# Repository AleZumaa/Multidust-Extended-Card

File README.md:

# Multidust-Extended-Card

## Placa Extensora / Breakout de Pruebas (Test Adapter Board)

Placa de circuito impreso (PCB) diseñada como interfaz de interconexión y depuración para medición, ruteo y diagnóstico de señales. Permite derivar conectores multicable de cinta plana (IDC / HE10) hacia puntos de prueba o pines header individuales (J1 a J130), facilitando el conexionado con osciloscopios, analizadores lógicos, multímetros o protoboards.

---

## 🛠️ Herramientas de Diseño (EDA)

* **Software:** [KiCad EDA](https://www.kicad.org/)
* **Versión:** `v10.0.1`

> ℹ️ **Nota de compatibilidad:** El esquema y el layout fueron diseñados con **KiCad 10.0.1**. Para abrir y editar los archivos de proyecto sin problemas de migración de footprints o bibliotecas de símbolos, se recomienda utilizar KiCad 10.0.1 o superior.

---

## 📋 Características Principales

- **Conectores Principales:**
  - `CONN-1`: IDC / HE10 hembra/macho de **40 pines** (`HE10-40-1`).
  - `CONN-2`: IDC / HE10 hembra/macho de **40 pines** (`HE10-40-2`).
  - `CONN-3`: IDC / HE10 hembra/macho de **40 pines** (`HE10-40-3`).
  - `CONN-4`: IDC / HE10 hembra/macho de **10 pines** (`HE10-10`).
- **Puntos de Medición / Breakout:**
  - 130 terminales individuales tipo pad / pin-header paso 2.54 mm (`J1` a `J130`).
  - Distribución en doble hilera perimétrica (izquierda/derecha) con pads cuadrados/redondos para facilitar la colocación de puntas de prueba o pines macho/hembra.
- **Topología de PCB:**
  - Placa de 2 capas (*Double-sided FR4*).
  - Pistas con trazado a 45° optimizado para mantener integridad de señal básica y separación uniforme.
  - Indicadores serigrafiados de orientación (flechas triangulares en pin 1 de cada conector IDC).

---

## 📐 Especificaciones Técnicas

| Parámetro | Valor / Descripción |
| :--- | :--- |
| **Tipo de Placa** | Breakout / Adapter / Test Board |
| **Software EDA** | **KiCad v10.0.1** |
| **Capas** | 2 capas (Top / Bottom) |
| **Material sugerido** | FR-4 estándar (1.6 mm espesor) |
| **Acabado sugerido** | HASL Lead-Free o ENIG (recomendado para pads de prueba) |
| **Paso de Conectores IDC** | 2.54 mm (0.1") |
| **Paso de Headers de Prueba** | 2.54 mm (0.1") estándar |
| **Capacidad de Señal** | Señales lógicas, buses digitales (GPIO, SPI, UART, I2C, bus paralelo) y alimentación de baja corriente |

---

## 🔌 Asignación de Conectores y Ruteo

| Conector | Tipo / Descripción | Rango de Pines Breakout |
| :---: | :---: | :---: |
| **CONN-1** | HE10-40 (40 pines) | `J1` – `J40` |
| **CONN-2** | HE10-40 (40 pines) | `J41` – `J80` |
| **CONN-3** | HE10-40 (40 pines) | `J81` – `J120` |
| **CONN-4** | HE10-10 (10 pines) | `J121` – `J130` |

> ⚠️ **Nota:** Verificar siempre la correspondencia entre la serigrafía (flecha de pin 1 en `CONN-1..4`) y la muesca polarizadora del cable plano IDC antes de alimentar el circuito bajo prueba.

---

## 🛠️ Lista de Materiales (BOM)

| Designador | Cantidad | Componente / Descripción | Encapsulado / Footprint |
| :--- | :---: | :--- | :--- |
| `CONN-1`, `CONN-2`, `CONN-3` | 3 | Conector Header tipo caja IDC 40 pines (2x20) paso 2.54 mm | Through-Hole (THT) 2.54 mm |
| `CONN-4` | 1 | Conector Header tipo caja IDC 10 pines (2x5) paso 2.54 mm | Through-Hole (THT) 2.54 mm |
| `J1` - `J130` | 130 | Tiras de pines hembra o macho / Puntos de prueba (Test Points) | Pad / THT individual 2.54 mm |

---

## 📁 Estructura del Repositorio

```text
├── Hardware/
│   ├── Schematics/         # Esquemáticos en formato KiCad v10.0.1 (.kicad_sch)
│   ├── PCB/                # Archivo de PCB KiCad v10.0.1 (.kicad_pcb)
│   └── Gerbers/            # Archivos de fabricación (Gerber RS-274X, Drill files)
├── Docs/
│   ├── Pinout_Mapping.csv  # Mapeo detallado señal por señal
│   └── Dimensions.pdf      # Plano mecánico acotado
└── README.md
```

---

## 📄 Licencia

Este hardware se distribuye bajo licencia libre [CERN-OHL-P](https://ohwr.org/cern_ohl_p_v2.txt) (Open Hardware Licence Permissive) o [MIT License](LICENSE).

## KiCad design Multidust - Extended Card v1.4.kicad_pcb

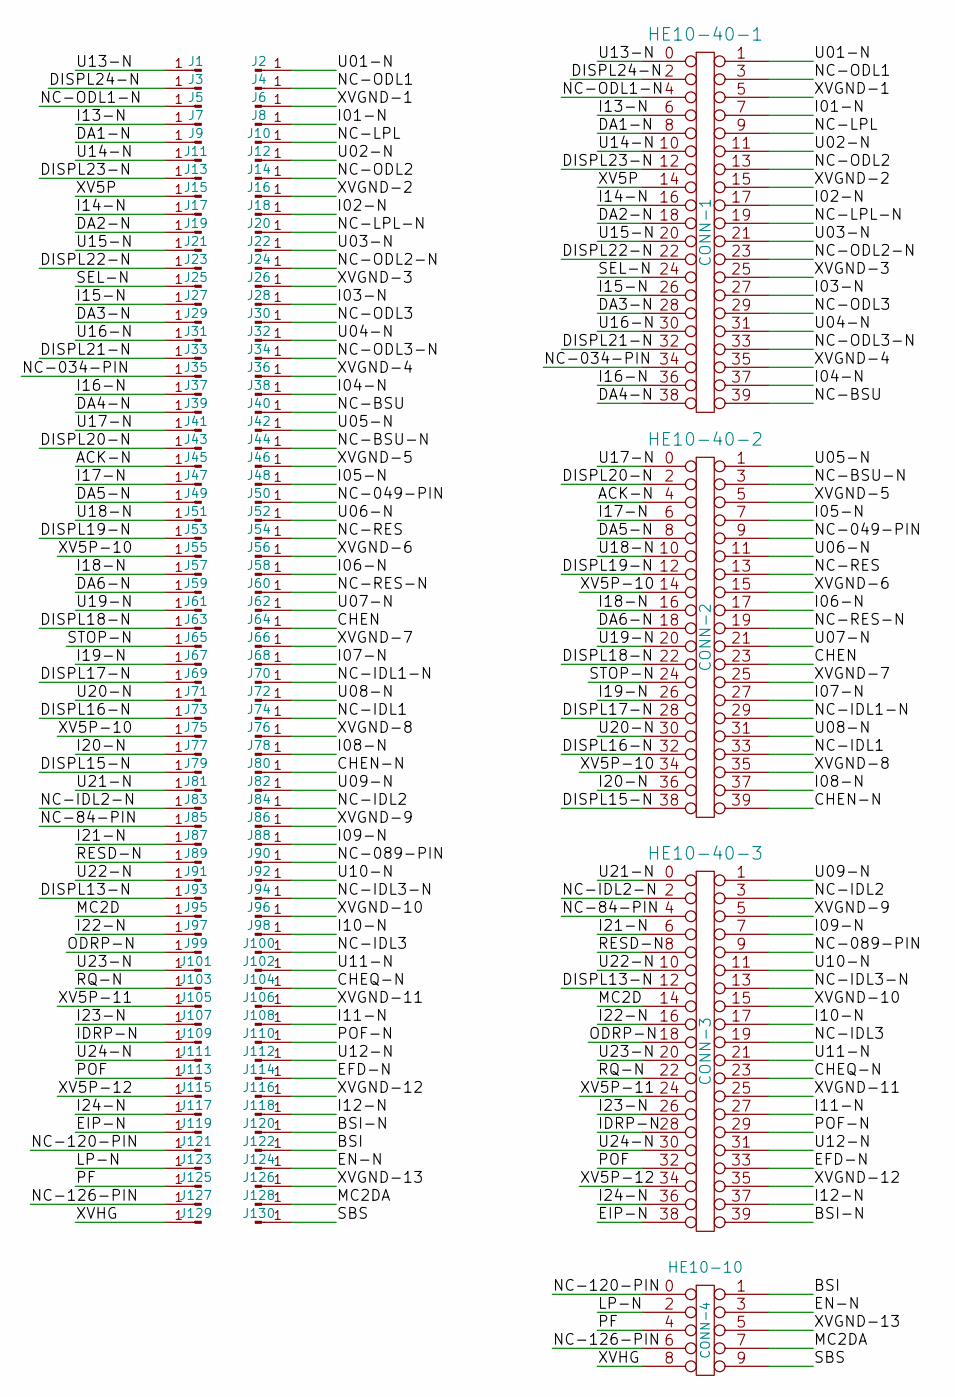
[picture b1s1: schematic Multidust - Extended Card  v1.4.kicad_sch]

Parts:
HE10-10: CONN-4; he10-10
HE10-40-1: CONN-1; he10-40
HE10-40-2: CONN-2; he10-40
HE10-40-3: CONN-3; he10-40
J1, J2, J3, J4, J5, J6, J7, J8, J9, J10, J11, J12, J13, J14, J15, J16, J17, J18, J19, J20, J21, J22, J23, J24, J25, J26, J27, J28, J29, J30, J31, J32, J33, J34, J35, J36, J37, J38, J39, J40, J41, J42, J43, J44, J45, J46, J47, J48, J49, J50, J51, J52, J53, J54, J55, J56, J57, J58, J59, J60, J61, J62, J63, J64, J65, J66, J67, J68, J69, J70, J71, J72, J73, J74, J75, J76, J77, J78, J79, J80, J81, J82, J83, J84, J85, J86, J87, J88, J89, J90, J91, J92, J93, J94, J95, J96, J97, J98, J99, J100, J101, J102, J103, J104, J105, J106, J107, J108, J109, J110, J111, J112, J113, J114, J115, J116, J117, J118, J119, J120, J121, J122, J123, J124, J125, J126, J127, J128, J129, J130: Conn_01x01_Pin; PinHeader_1x01_Oval_Grande

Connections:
/ACK-N: HE10-40-2.4, J45.1 (Pin_1_1)
/BSI: HE10-10.1, J122.1 (Pin_1_1)
/BSI-N: HE10-40-3.39, J120.1 (Pin_1_1)
/CHEN: HE10-40-2.23, J64.1 (Pin_1_1)
/CHEN-N: HE10-40-2.39, J80.1 (Pin_1_1)
/CHEQ-N: HE10-40-3.23, J104.1 (Pin_1_1)
/DA1-N: HE10-40-1.8, J9.1 (Pin_1_1)
/DA2-N: HE10-40-1.18, J19.1 (Pin_1_1)
/DA3-N: HE10-40-1.28, J29.1 (Pin_1_1)
/DA4-N: HE10-40-1.38, J39.1 (Pin_1_1)
/DA5-N: HE10-40-2.8, J49.1 (Pin_1_1)
/DA6-N: HE10-40-2.18, J59.1 (Pin_1_1)
/DISPL13-N: HE10-40-3.12, J93.1 (Pin_1_1)
/DISPL15-N: HE10-40-2.38, J79.1 (Pin_1_1)
/DISPL16-N: HE10-40-2.32, J73.1 (Pin_1_1)
/DISPL17-N: HE10-40-2.28, J69.1 (Pin_1_1)
/DISPL18-N: HE10-40-2.22, J63.1 (Pin_1_1)
/DISPL19-N: HE10-40-2.12, J53.1 (Pin_1_1)
/DISPL20-N: HE10-40-2.2, J43.1 (Pin_1_1)
/DISPL21-N: HE10-40-1.32, J33.1 (Pin_1_1)
/DISPL22-N: HE10-40-1.22, J23.1 (Pin_1_1)
/DISPL23-N: HE10-40-1.12, J13.1 (Pin_1_1)
/DISPL24-N: HE10-40-1.2, J3.1 (Pin_1_1)
/EFD-N: HE10-40-3.33, J114.1 (Pin_1_1)
/EIP-N: HE10-40-3.38, J119.1 (Pin_1_1)
/EN-N: HE10-10.3, J124.1 (Pin_1_1)
/I01-N: HE10-40-1.7, J8.1 (Pin_1_1)
/I02-N: HE10-40-1.17, J18.1 (Pin_1_1)
/I03-N: HE10-40-1.27, J28.1 (Pin_1_1)
/I04-N: HE10-40-1.37, J38.1 (Pin_1_1)
/I05-N: HE10-40-2.7, J48.1 (Pin_1_1)
/I06-N: HE10-40-2.17, J58.1 (Pin_1_1)
/I07-N: HE10-40-2.27, J68.1 (Pin_1_1)
/I08-N: HE10-40-2.37, J78.1 (Pin_1_1)
/I09-N: HE10-40-3.7, J88.1 (Pin_1_1)
/I10-N: HE10-40-3.17, J98.1 (Pin_1_1)
/I11-N: HE10-40-3.27, J108.1 (Pin_1_1)
/I12-N: HE10-40-3.37, J118.1 (Pin_1_1)
/I13-N: HE10-40-1.6, J7.1 (Pin_1_1)
/I14-N: HE10-40-1.16, J17.1 (Pin_1_1)
/I15-N: HE10-40-1.26, J27.1 (Pin_1_1)
/I16-N: HE10-40-1.36, J37.1 (Pin_1_1)
/I17-N: HE10-40-2.6, J47.1 (Pin_1_1)
/I18-N: HE10-40-2.16, J57.1 (Pin_1_1)
/I19-N: HE10-40-2.26, J67.1 (Pin_1_1)
/I20-N: HE10-40-2.36, J77.1 (Pin_1_1)
/I21-N: HE10-40-3.6, J87.1 (Pin_1_1)
/I22-N: HE10-40-3.16, J97.1 (Pin_1_1)
/I23-N: HE10-40-3.26, J107.1 (Pin_1_1)
/I24-N: HE10-40-3.36, J117.1 (Pin_1_1)
/IDRP-N: HE10-40-3.28, J109.1 (Pin_1_1)
/LP-N: HE10-10.2, J123.1 (Pin_1_1)
/MC2D: HE10-40-3.14, J95.1 (Pin_1_1)
/MC2DA: HE10-10.7, J128.1 (Pin_1_1)
/NC-034-PIN: HE10-40-1.34, J35.1 (Pin_1_1)
/NC-049-PIN: HE10-40-2.9, J50.1 (Pin_1_1)
/NC-84-PIN: HE10-40-3.4, J85.1 (Pin_1_1)
/NC-089-PIN: HE10-40-3.9, J90.1 (Pin_1_1)
/NC-120-PIN: HE10-10.0, J121.1 (Pin_1_1)
/NC-126-PIN: HE10-10.6, J127.1 (Pin_1_1)
/NC-BSU: HE10-40-1.39, J40.1 (Pin_1_1)
/NC-BSU-N: HE10-40-2.3, J44.1 (Pin_1_1)
/NC-IDL1: HE10-40-2.33, J74.1 (Pin_1_1)
/NC-IDL1-N: HE10-40-2.29, J70.1 (Pin_1_1)
/NC-IDL2: HE10-40-3.3, J84.1 (Pin_1_1)
/NC-IDL2-N: HE10-40-3.2, J83.1 (Pin_1_1)
/NC-IDL3: HE10-40-3.19, J100.1 (Pin_1_1)
/NC-IDL3-N: HE10-40-3.13, J94.1 (Pin_1_1)
/NC-LPL: HE10-40-1.9, J10.1 (Pin_1_1)
/NC-LPL-N: HE10-40-1.19, J20.1 (Pin_1_1)
/NC-ODL1: HE10-40-1.3, J4.1 (Pin_1_1)
/NC-ODL1-N: HE10-40-1.4, J5.1 (Pin_1_1)
/NC-ODL2: HE10-40-1.13, J14.1 (Pin_1_1)
/NC-ODL2-N: HE10-40-1.23, J24.1 (Pin_1_1)
/NC-ODL3: HE10-40-1.29, J30.1 (Pin_1_1)
/NC-ODL3-N: HE10-40-1.33, J34.1 (Pin_1_1)
/NC-RES: HE10-40-2.13, J54.1 (Pin_1_1)
/NC-RES-N: HE10-40-2.19, J60.1 (Pin_1_1)
/ODRP-N: HE10-40-3.18, J99.1 (Pin_1_1)
/PF: HE10-10.4, J125.1 (Pin_1_1)
/POF: HE10-40-3.32, J113.1 (Pin_1_1)
/POF-N: HE10-40-3.29, J110.1 (Pin_1_1)
/RESD-N: HE10-40-3.8, J89.1 (Pin_1_1)
/RQ-N: HE10-40-3.22, J103.1 (Pin_1_1)
/SBS: HE10-10.9, J130.1 (Pin_1_1)
/SEL-N: HE10-40-1.24, J25.1 (Pin_1_1)
/STOP-N: HE10-40-2.24, J65.1 (Pin_1_1)
/U01-N: HE10-40-1.1, J2.1 (Pin_1_1)
/U02-N: HE10-40-1.11, J12.1 (Pin_1_1)
/U03-N: HE10-40-1.21, J22.1 (Pin_1_1)
/U04-N: HE10-40-1.31, J32.1 (Pin_1_1)
/U05-N: HE10-40-2.1, J42.1 (Pin_1_1)
/U06-N: HE10-40-2.11, J52.1 (Pin_1_1)
/U07-N: HE10-40-2.21, J62.1 (Pin_1_1)
/U08-N: HE10-40-2.31, J72.1 (Pin_1_1)
/U09-N: HE10-40-3.1, J82.1 (Pin_1_1)
/U10-N: HE10-40-3.11, J92.1 (Pin_1_1)
/U11-N: HE10-40-3.21, J102.1 (Pin_1_1)
/U12-N: HE10-40-3.31, J112.1 (Pin_1_1)
/U13-N: HE10-40-1.0, J1.1 (Pin_1_1)
/U14-N: HE10-40-1.10, J11.1 (Pin_1_1)
/U15-N: HE10-40-1.20, J21.1 (Pin_1_1)
/U16-N: HE10-40-1.30, J31.1 (Pin_1_1)
/U17-N: HE10-40-2.0, J41.1 (Pin_1_1)
/U18-N: HE10-40-2.10, J51.1 (Pin_1_1)
/U19-N: HE10-40-2.20, J61.1 (Pin_1_1)
/U20-N: HE10-40-2.30, J71.1 (Pin_1_1)
/U21-N: HE10-40-3.0, J81.1 (Pin_1_1)
/U22-N: HE10-40-3.10, J91.1 (Pin_1_1)
/U23-N: HE10-40-3.20, J101.1 (Pin_1_1)
/U24-N: HE10-40-3.30, J111.1 (Pin_1_1)
/XV5P: HE10-40-1.14, J15.1 (Pin_1_1)
/XV5P-3: HE10-40-3.24, J105.1 (Pin_1_1)
/XV5P-4: HE10-40-3.34, J115.1 (Pin_1_1)
/XVGND-1: HE10-40-1.5, J6.1 (Pin_1_1)
/XVGND-2: HE10-40-1.15, J16.1 (Pin_1_1)
/XVGND-3: HE10-40-1.25, J26.1 (Pin_1_1)
/XVGND-4: HE10-40-1.35, J36.1 (Pin_1_1)
/XVGND-5: HE10-40-2.5, J46.1 (Pin_1_1)
/XVGND-6: HE10-40-2.15, J56.1 (Pin_1_1)
/XVGND-7: HE10-40-2.25, J66.1 (Pin_1_1)
/XVGND-8: HE10-40-2.35, J76.1 (Pin_1_1)
/XVGND-9: HE10-40-3.5, J86.1 (Pin_1_1)
/XVGND-10: HE10-40-3.15, J96.1 (Pin_1_1)
/XVGND-11: HE10-40-3.25, J106.1 (Pin_1_1)
/XVGND-12: HE10-40-3.35, J116.1 (Pin_1_1)
/XVGND-13: HE10-10.5, J126.1 (Pin_1_1)
/XVHG: HE10-10.8, J129.1 (Pin_1_1)

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
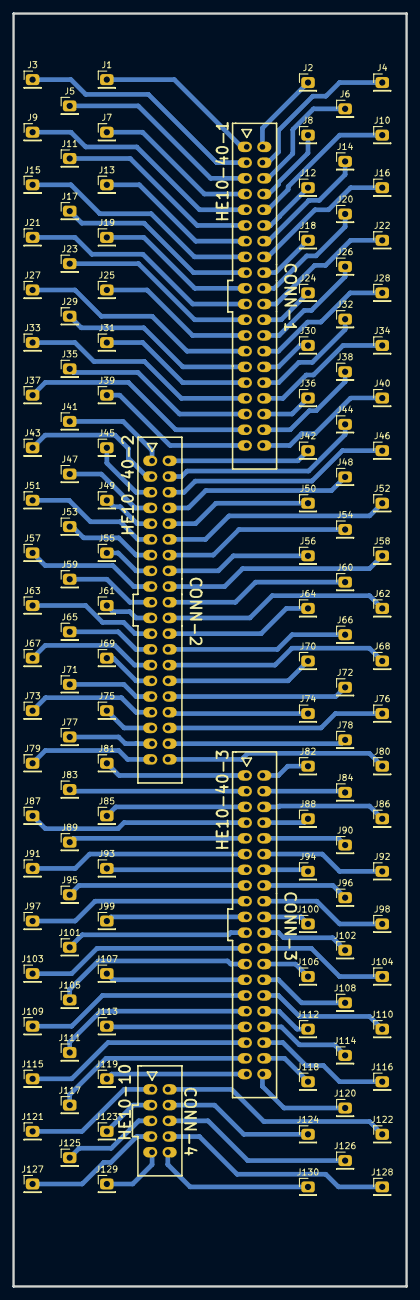
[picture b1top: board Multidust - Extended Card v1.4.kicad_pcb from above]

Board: 4 copper layers, 63.5 x 205.7 mm, 134 parts (0 on the bottom side), 130 nets.
